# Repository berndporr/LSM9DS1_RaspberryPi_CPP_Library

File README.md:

# I2C LSM9DS1 RaspberryPI C++ Library

This is a C++11 library for the LSM9DS1 on a Raspberry PI using a callback handler for the data.
The callback handler is called at the sampling rate of the gyroscope of the LSM9DS1.

It's based on the [SparkFun_LSM9DS1_Arduino_Library](https://github.com/sparkfun/SparkFun_LSM9DS1_Arduino_Library).

Included is also a PCB design to connect the IMU with a long cable via level shifters to the Raspberry PI.

## Hardware

You can use the [SparkFun 9DoF IMU Breakout board](https://www.sparkfun.com/products/13284)
or make your own PCB (see the `pcbs` folder).

  - Connect the 3.3V power (pin 1) and GND (pin 9) to the LSM9DS1.
  - Connect the I2C SDA (pin 3) & I2C SCL (pin 5) to the LSM9DS1.
  - Connect the GPIO22 (pin 15) to the INT2 output of the LSM9DS1.

## Software requirement

```
sudo apt-get install libpigpio-dev
```

## Install

Run `raspi-config` and enable i2c.

If you are not the `pi` user make sure that in `/etc/group` you are member of the `i2c`-group.

```
cmake .
make
sudo make install
sudo ldconfig
```

## Example / test

```
cd example
sudo ./LSM9DS1_demo
```

## Documentation

The relevant public sections of the header files have docstrings.

The online documentation is here: https://berndporr.github.io/LSM9DS1_RaspberryPi_CPP_Library/

This demo runs with a callback handler and it's called at the default sampling rate of 50Hz.

## PCBs

The subdirectory PCBs contains two PCBs: one hat which plugs into the
raspberry PI and the PCB which contains the IMU. The PCBs are connected
via a standard telephone cable and can be over 10m long.

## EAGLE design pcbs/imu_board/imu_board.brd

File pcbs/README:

PCBs to connect the LSM9DS1 over a long standard telephone cable.
The hat goes on the Rapberry PI and the imu_board connects
to it via the telephone cable.

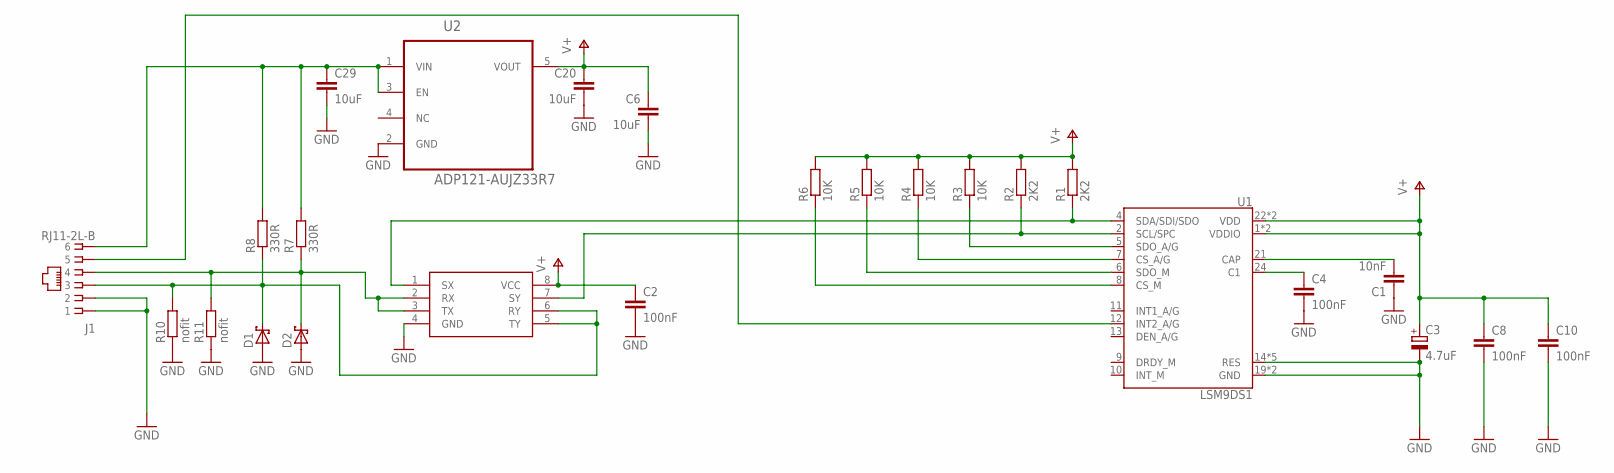
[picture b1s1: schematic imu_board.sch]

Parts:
C1: 10nF; C0805
C2, C4, C8, C10: 100nF; C0805
C3: 4.7uF; SMC_C
C6, C20, C29: 10uF; C1206
D1, D2: SCHOTTKY-DIODE; DIODE_SMB
J1: RJ11-2L-B; RJ11-NO_SHIELD
R1, R2: 2K2; R0805
R3, R4, R5, R6: 10K; R0805
R7, R8: 330R; R0805
R10, R11: nofit; R1206
U1: LSM9DS1; LGA24-8X4
U2: ADP121-AUJZ33R7; SOT95P280X100-5N
U$1: P82B96; DIP8

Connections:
GND: C1.1, C2.2, C3.-, C4.2, C6.2, C8.2, C10.2, C20.2, C29.2, D1.A (C), D2.A (C), J1.1, J1.2, R10.1, R11.1, U1.14 (RES), U1.15 (RES), U1.16 (RES), U1.17 (RES), U1.18 (RES), U1.19 (GND), U1.20 (GND), U2.2 (GND), U$1.4 (GND)
unnamed: C1.2, U1.21 (CAP)
unnamed: C4.1, U1.24 (C1)
unnamed: J1.5, U1.12 (INT2_A/G)
unnamed: R3.1, U1.5 (SDO_A/G)
unnamed: R4.1, U1.7 (CS_A/G)
unnamed: R5.1, U1.6 (SDO_M)
unnamed: R6.1, U1.8 (CS_M)
unnamed: D2.C (A), J1.4, R7.1, R11.2, U$1.2 (RX), U$1.3 (TX)
unnamed: D1.C (A), J1.3, R8.1, R10.2, U$1.5 (TY), U$1.6 (RY)
unnamed: C29.1, J1.6, R7.2, R8.2, U2.1 (VIN), U2.3 (EN)
SCL: R2.1, U1.2 (SCL/SPC), U$1.7 (SY)
SDA: R1.1, U1.4 (SDA/SDI/SDO), U$1.1 (SX)
V+: C2.1, C3.+, C6.1, C8.1, C10.1, C20.1, R1.2, R2.2, R3.2, R4.2, R5.2, R6.2, U1.1 (VDDIO), U1.3 (VDDIO), U1.22 (VDD), U1.23 (VDD), U2.5 (VOUT), U$1.8 (VCC)

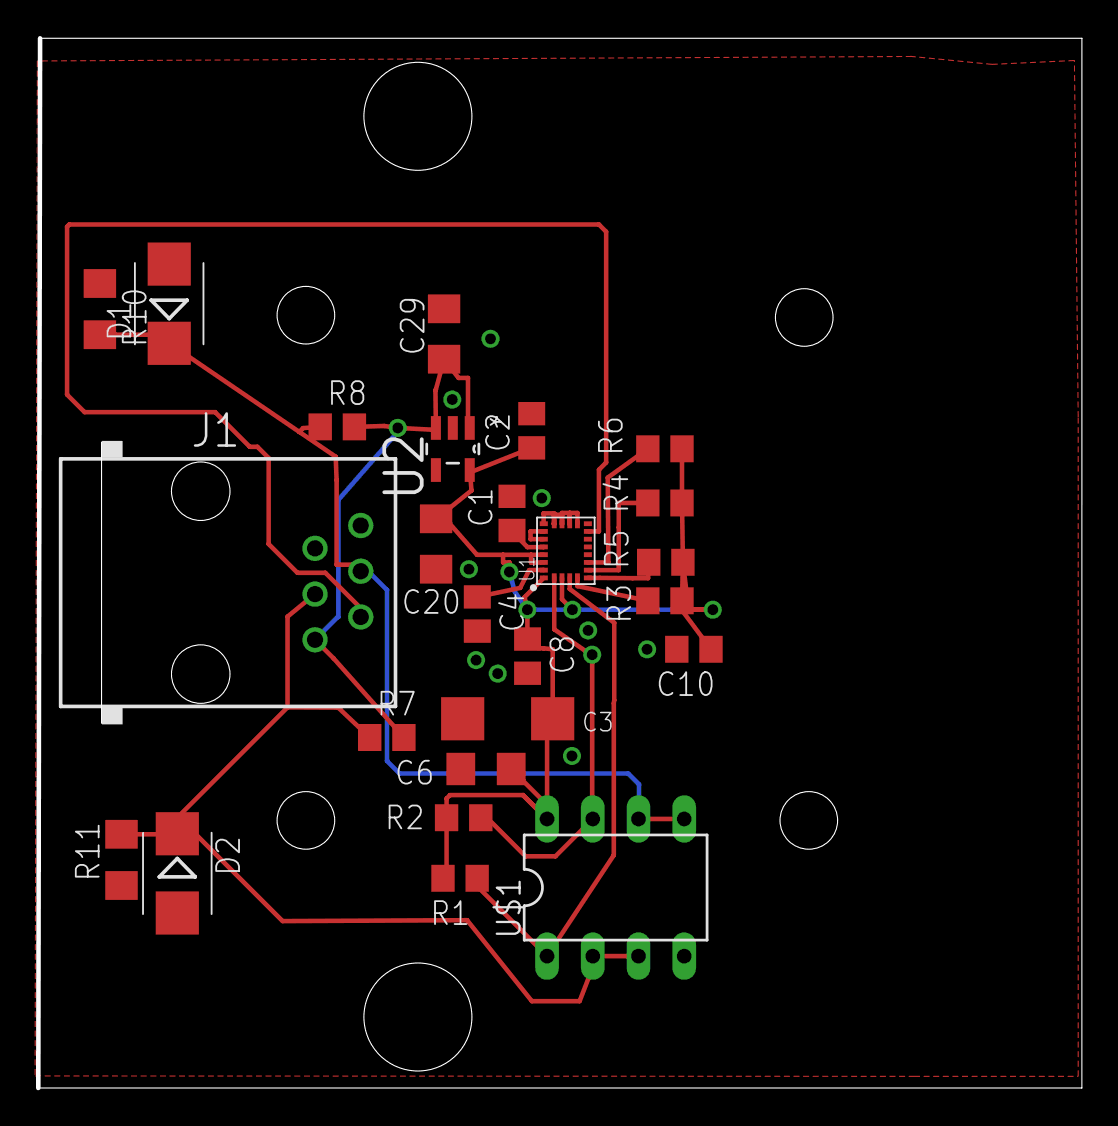
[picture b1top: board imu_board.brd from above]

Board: 2 copper layers, 57.9 x 58.3 mm, 25 parts (0 on the bottom side), 14 nets.

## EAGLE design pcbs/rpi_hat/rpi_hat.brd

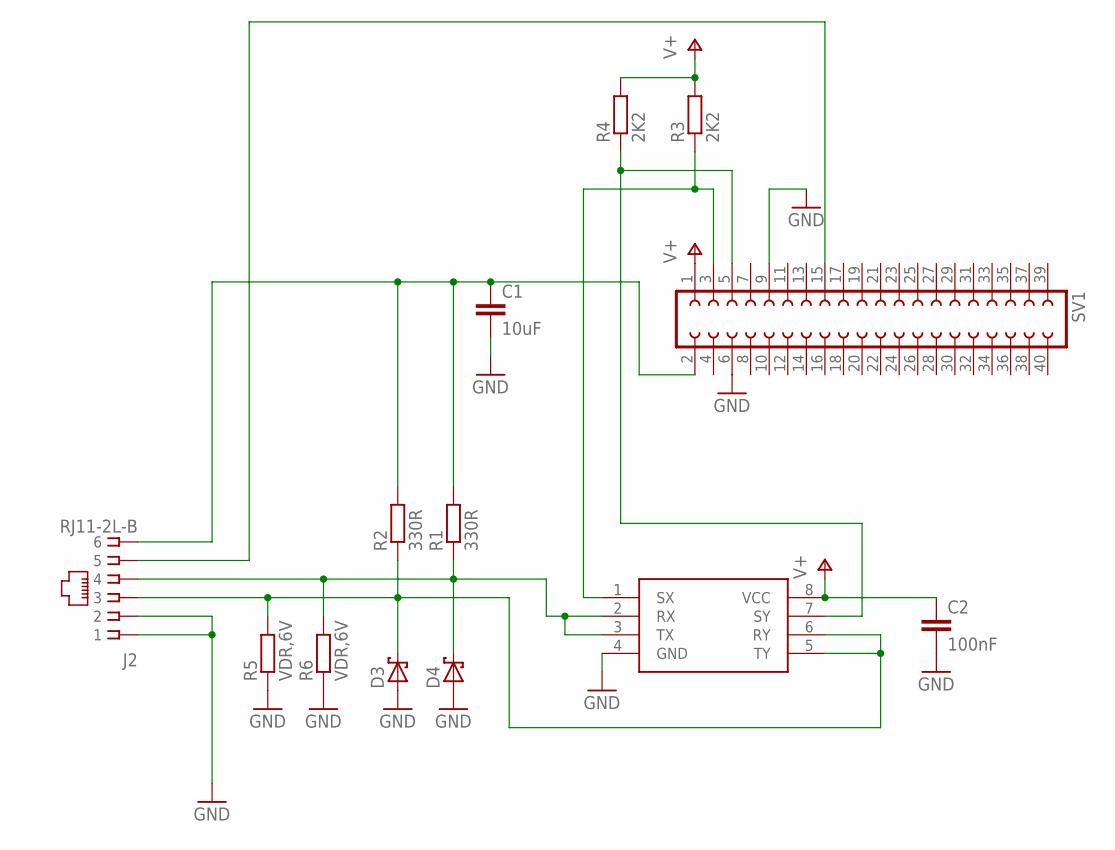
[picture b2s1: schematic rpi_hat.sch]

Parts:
C1: 10uF; C0805
C2: 100nF; C0805
D3, D4: SCHOTTKY-DIODE; DIODE_SMB
J2: RJ11-2L-B; RJ11-NO_SHIELD
R1, R2: 330R; R0805
R3, R4: 2K2; R0805
R5, R6: VDR,6V; R1206
SV1: FE20-2
U$2: P82B96; DIP8

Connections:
GND: C1.2, C2.2, D3.A (C), D4.A (C), J2.1, J2.2, R5.1, R6.1, SV1.6, SV1.9, U$2.4 (GND)
unnamed: C1.1, J2.6, R1.2, R2.2, SV1.2
unnamed: D4.C (A), J2.4, R1.1, R6.2, U$2.2 (RX), U$2.3 (TX)
unnamed: J2.5, SV1.15
unnamed: D3.C (A), J2.3, R2.1, R5.2, U$2.5 (TY), U$2.6 (RY)
SCL: R4.1, SV1.5, U$2.7 (SY)
SDA: R3.1, SV1.3, U$2.1 (SX)
V+: C2.1, R3.2, R4.2, SV1.1, U$2.8 (VCC)

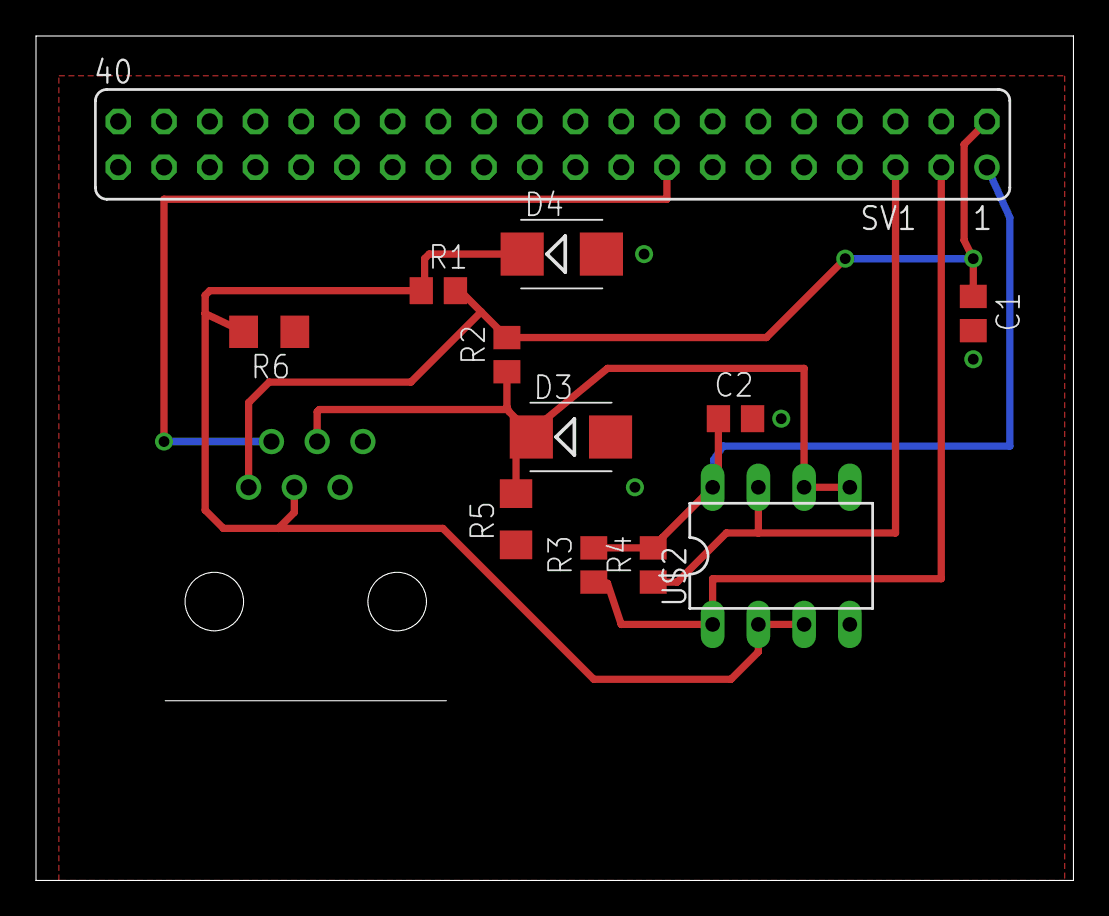
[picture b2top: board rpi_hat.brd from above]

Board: 2 copper layers, 57.6 x 46.9 mm, 13 parts (1 on the bottom side), 8 nets.

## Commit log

2020-01-30 Now with callback handler and C++ only.
2020-01-30 Fixed doc issues
2020-01-30 Added ldconfig
2020-01-30 Made clear that it's different to the original library.
2020-01-30 Made the title a bit nicer
2020-01-30 Added C++
2020-02-04 Changed to timer instead of polling for new data
2020-02-05 Added PCB designs
2020-02-05 Removed reference to the breakout board
2021-02-09 Added info about i2c config.
2022-02-13 Replaced wiringPI with pigpio
2022-02-13 Added more tidy up stuff
2022-02-13 Changed pointer to pigpio
2022-02-13 Removed timer and the DRDY line triggers now a proper interrupt.
2022-02-13 Added the dataready line
2022-02-13 Updated wiring
2022-02-13 Removed debug outputs
2022-02-13 Added info about the sampling rate
2022-02-13 Moved the initisalisers
2022-02-13 Tidies up the settings
2022-02-13 Updated docs
2022-02-13 Created a sample datatype
2022-02-13 Fixed demo so that it takes the sample struct
2022-02-13 Added beerware license
2022-02-13 Added doxyfile
2022-02-13 Added docstrings
2022-02-13 Added script for debug compilation.
2022-02-13 Removed overhead
2022-02-13 Regenerated the docs
2022-02-13 Changed comm to bare bones i2c
2022-02-14 Removed pigpio and replaced with sysfs but needs proper debugging.
2022-02-14 All working now!
2022-02-14 cpp was missing
2022-02-14 Changed to a class
2022-02-14 GPIO sysfs is now a class
2022-02-14 Updated version
2022-02-14 Added missing pin and missing unexport
2022-02-14 Back to pigpio
2022-02-14 Fixed the gpio22
2022-02-14 Added temperature
2022-02-14 New docs
2022-02-15 Needs sudo
2022-02-15 Got rid of any dangerous int8 constants
2022-02-15 updated doc
2022-02-17 Temperature was rounding a bit too much!
2022-02-17 Redundant info
2025-01-24 Got rid of the old pigpio library and replaced with libgpiod
2025-01-25 i2c transfer works but needs testing
2025-01-25 Made sure exit works but still the converter can't be reset
2025-01-25 Reads now all channels
